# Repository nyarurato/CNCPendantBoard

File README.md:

# CNCPendantBoard

## Description
These are Eagle files for the substrate using CNC pendant with CNCjs and Duet.
You can use a CNC Pendant on CNCjs and Duet Board.

For more information: https://bbs.avalontech.jp/t/cnc/718

## Licence

[CC BY-SA 4.0](https://creativecommons.org/licenses/by-sa/4.0/)

## Author

[nyarurato](https://github.com/nyarurato)

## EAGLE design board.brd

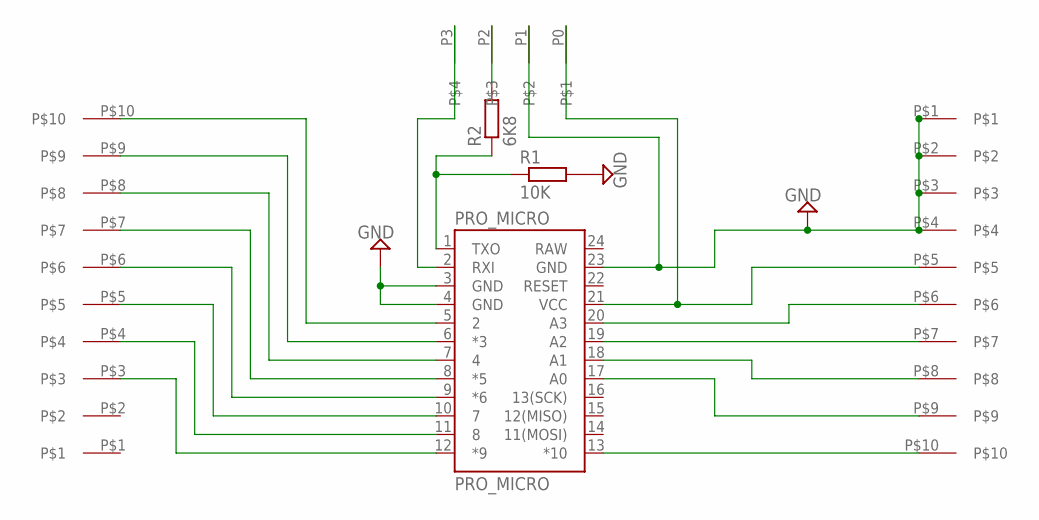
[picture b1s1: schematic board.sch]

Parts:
PRO_MICRO: PRO_MICRO; SPARKFUN_PRO_MICRO
R1: 10K; R0805
R2: 6K8; R0805
U$1, U$2: TERMINAL10
U$3: TERMINAL4

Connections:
GND: PRO_MICRO.3 (GND), PRO_MICRO.4 (GND), PRO_MICRO.23 (GND), R1.2, U$2.P$1, U$2.P$2, U$2.P$3, U$2.P$4, U$3.P1
unnamed: PRO_MICRO.5 (2), U$1.P$10
unnamed: PRO_MICRO.6 (*3), U$1.P$9
unnamed: PRO_MICRO.7 (4), U$1.P$8
unnamed: PRO_MICRO.8 (*5), U$1.P$7
unnamed: PRO_MICRO.9 (*6), U$1.P$6
unnamed: PRO_MICRO.10 (7), U$1.P$5
unnamed: PRO_MICRO.11 (8), U$1.P$4
unnamed: PRO_MICRO.12 (*9), U$1.P$3
unnamed: PRO_MICRO.13 (*10), U$2.P$10
unnamed: PRO_MICRO.17 (A0), U$2.P$9
unnamed: PRO_MICRO.18 (A1), U$2.P$8
unnamed: PRO_MICRO.19 (A2), U$2.P$7
unnamed: PRO_MICRO.20 (A3), U$2.P$6
unnamed: PRO_MICRO.1 (TXO), R1.1, R2.1
unnamed: PRO_MICRO.2 (RXI), U$3.P3
unnamed: R2.2, U$3.P2
RAW: PRO_MICRO.24 (RAW)
VCC: PRO_MICRO.21 (VCC), U$2.P$5, U$3.P0

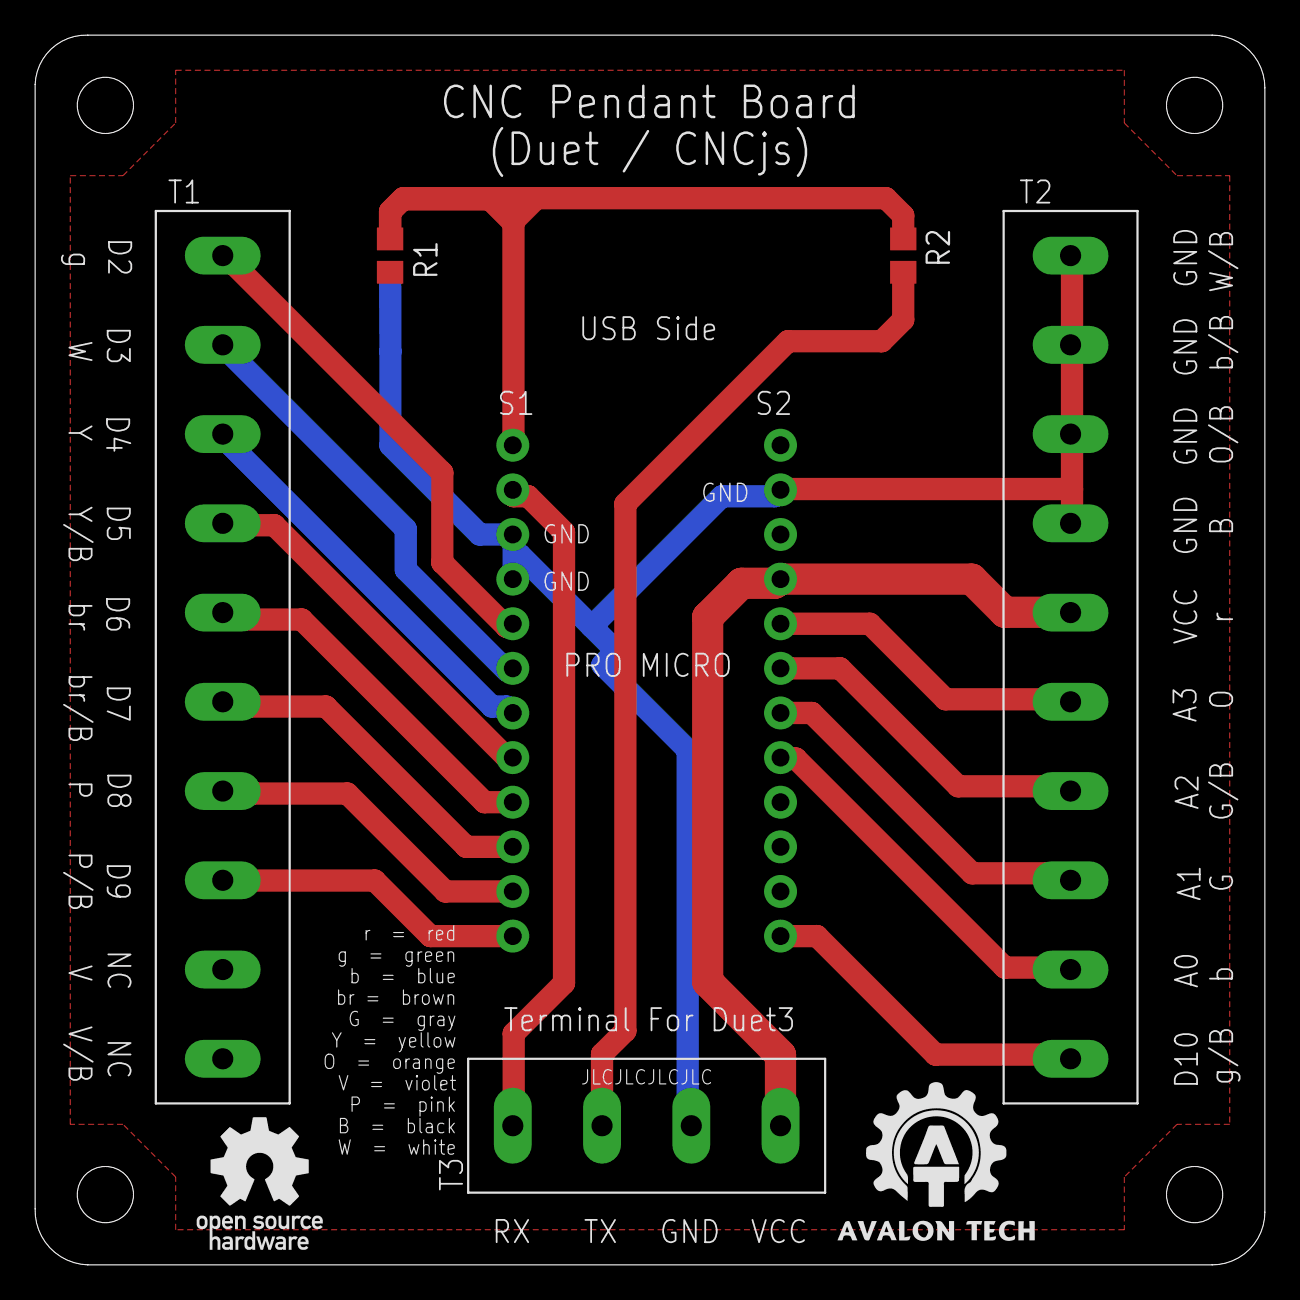
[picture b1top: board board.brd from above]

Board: 2 copper layers, 70.0 x 70.0 mm, 6 parts (0 on the bottom side), 18 nets.

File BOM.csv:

"Part";"Value";"Device";"Package";"Description";"POPULARITY";"SPICEPREFIX";
"PRO_MICRO";"PRO_MICRO";"SPARKFUN_PRO_MICRO";"SPARKFUN_PRO_MICRO";"SparkFun Pro Micro";"";"";
"R1";"10K";"R-EU_0207/10";"0207/10";"RESISTOR, European symbol";"81";"R";
"R2";"6K8";"R-EU_0207/10";"0207/10";"RESISTOR, European symbol";"81";"R";
"U$1";"KF141V-2.54-10P";"KF141V-2.54-10P";"KF141V-2.54-10P";"";"";"";
"U$2";"KF141V-2.54-10P";"KF141V-2.54-10P";"KF141V-2.54-10P";"";"";"";
"U$3";"TERMINAL4";"TERMINAL4";"TERMINAL4";"";"";"";

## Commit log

2020-11-09 Add eagle files and images
2020-11-09 update README first time
2020-11-09 set LICENSE
2022-03-30 v1.1
2023-11-27 update gitignore
2023-11-28 update for jlcpcb pcba

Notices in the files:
parts and their libraries:
SparkFun-Boards: Licensing: Creative Commons ShareAlike 4.0 International - https://creativecommons.org/licenses/by-sa/4.0
